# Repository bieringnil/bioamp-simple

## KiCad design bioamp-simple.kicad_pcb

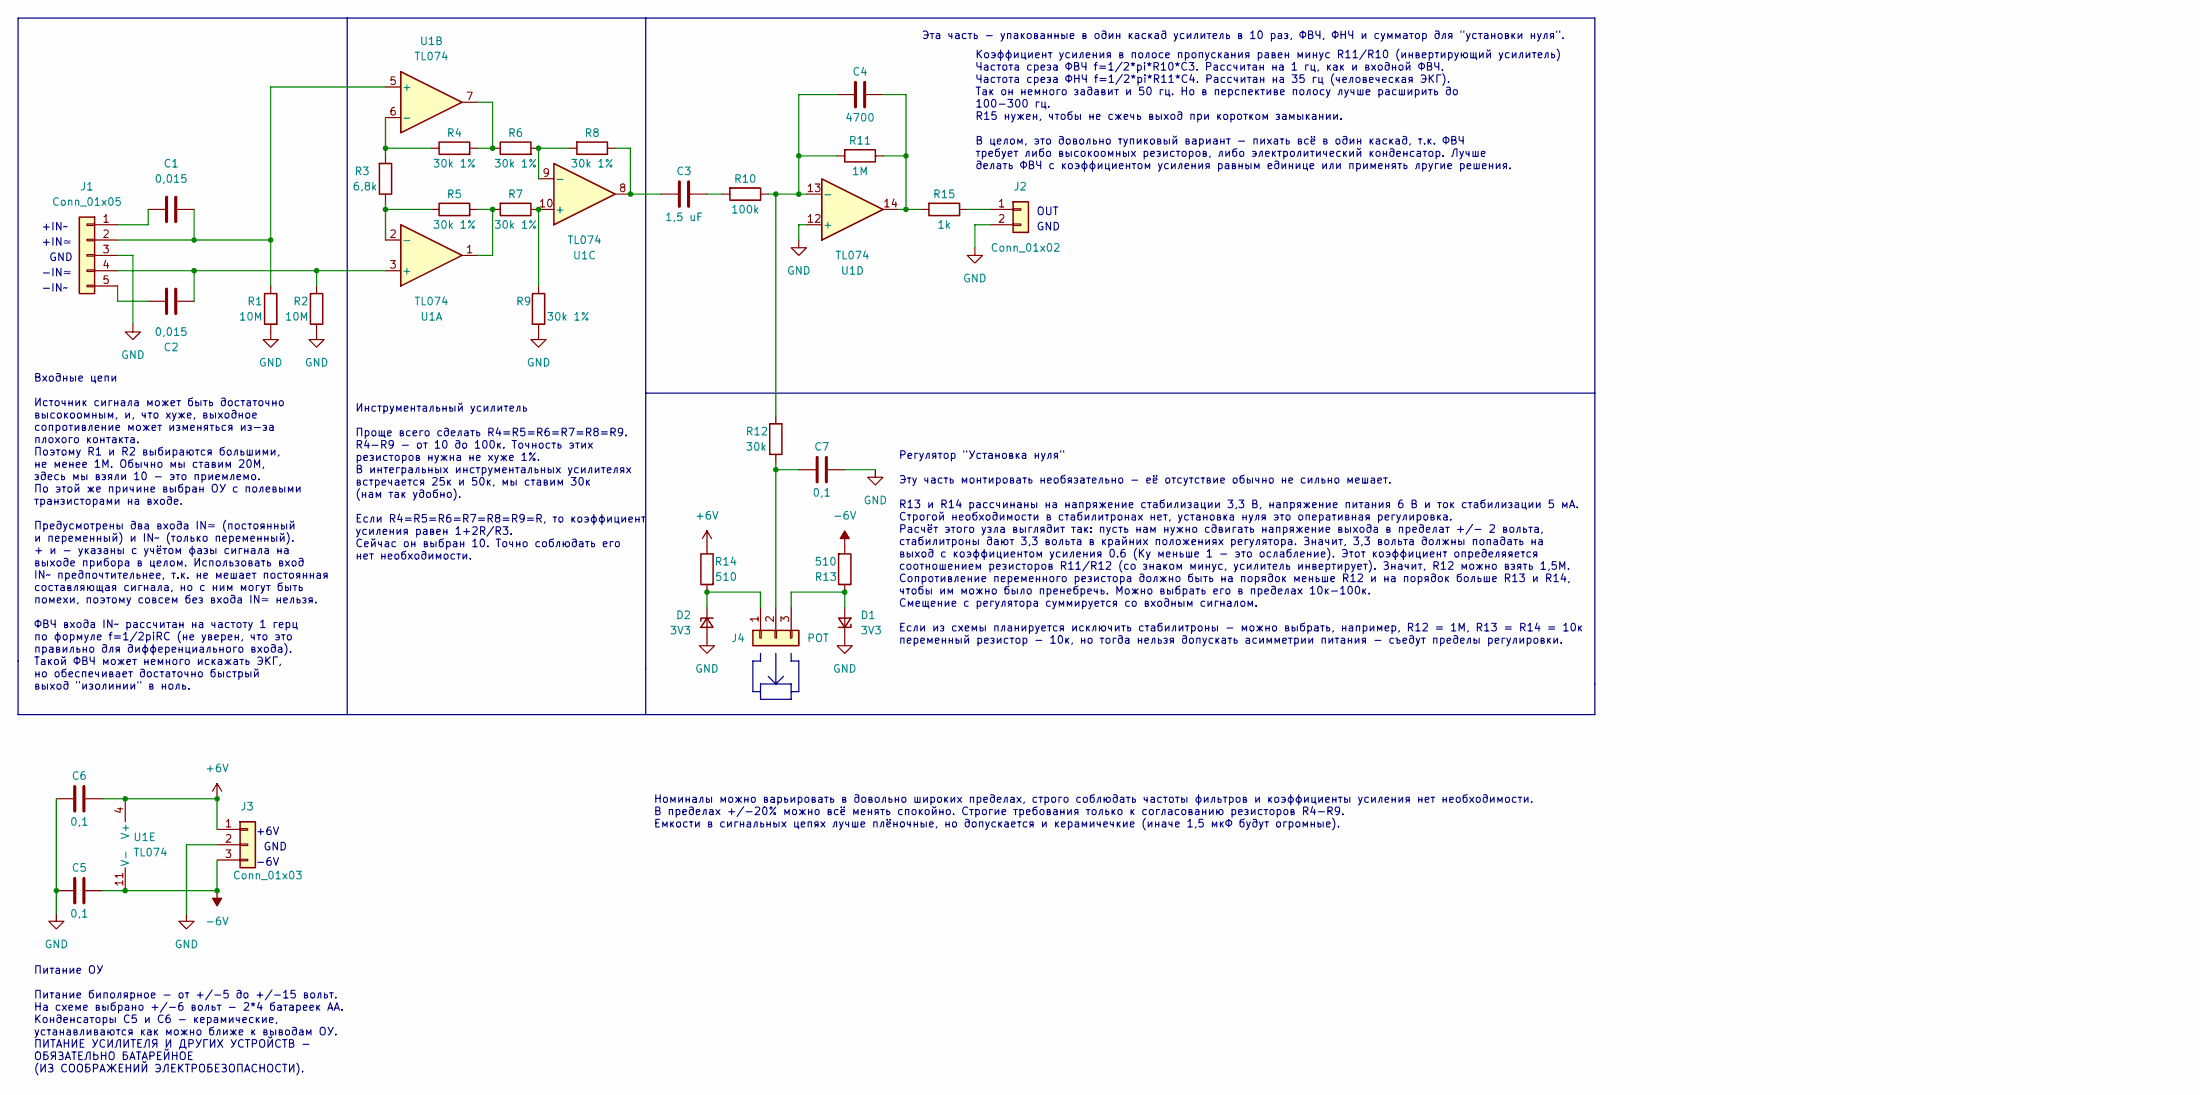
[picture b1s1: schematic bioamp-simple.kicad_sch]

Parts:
C1, C2: 0,015; C_Rect_L7.0mm_W4.5mm_P5.00mm
C3: 1,5 uF; C_Rect_L16.5mm_W5.0mm_P15.00mm_MKT
C4: 4700; C_Rect_L7.0mm_W4.5mm_P5.00mm
C5, C6, C7: 0,1; C_Rect_L7.0mm_W4.5mm_P5.00mm
D1, D2: 3V3; D_A-405_P10.16mm_Horizontal
J1: Conn_01x05; SolderWire-0.5sqmm_1x05_P4.6mm_D0.9mm_OD2.1mm
J2: Conn_01x02; SolderWire-0.5sqmm_1x02_P4.6mm_D0.9mm_OD2.1mm
J3: Conn_01x03; SolderWire-0.5sqmm_1x03_P4.6mm_D0.9mm_OD2.1mm
J4: POT; SolderWire-0.5sqmm_1x03_P4.6mm_D0.9mm_OD2.1mm
R1, R2: 10M; R_Axial_DIN0207_L6.3mm_D2.5mm_P15.24mm_Horizontal
R3: 6,8k; R_Axial_DIN0207_L6.3mm_D2.5mm_P10.16mm_Horizontal
R4, R5, R8: 30k 1%; R_Axial_DIN0207_L6.3mm_D2.5mm_P2.54mm_Vertical
R6, R7, R9: 30k 1%; R_Axial_DIN0207_L6.3mm_D2.5mm_P10.16mm_Horizontal
R10: 100k; R_Axial_DIN0207_L6.3mm_D2.5mm_P10.16mm_Horizontal
R11: 1M; R_Axial_DIN0207_L6.3mm_D2.5mm_P2.54mm_Vertical
R12: 30k; R_Axial_DIN0207_L6.3mm_D2.5mm_P10.16mm_Horizontal
R13, R14: 510; R_Axial_DIN0207_L6.3mm_D2.5mm_P10.16mm_Horizontal
R15: 1k; R_Axial_DIN0207_L6.3mm_D2.5mm_P10.16mm_Horizontal
U1: TL074; DIP-14_W7.62mm_LongPads

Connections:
+6V: C6.2, J3.1, R14.1, U1.4 (V+)
-6V: C5.2, J3.3, R13.2, U1.11 (V-)
GND: C5.1, C6.1, C7.2, D1.1 (K), D2.2 (A), J1.3, J2.2, J3.2, R1.2, R2.1, R9.2, U1.12 (+)
unnamed: C3.1, R8.1, U1.8
unnamed: C3.2, R10.2
unnamed: C4.2, R11.1, R15.2, U1.14
unnamed: D1.2 (A), J4.3, R13.1
unnamed: D2.1 (K), J4.1, R14.2
unnamed: C1.1, J1.1
unnamed: C1.2, J1.2, R1.1, U1.5 (+)
unnamed: C2.2, J1.4, R2.2, U1.3 (+)
unnamed: C2.1, J1.5
unnamed: J2.1, R15.1
unnamed: C7.1, J4.2, R12.2
unnamed: R4.2, R6.1, U1.7
unnamed: R5.2, R7.2, U1.1
unnamed: R3.1, R5.1, U1.2 (-)
unnamed: R3.2, R4.1, U1.6 (-)
unnamed: R7.1, R9.1, U1.10 (+)
unnamed: R6.2, R8.2, U1.9 (-)
unnamed: C4.1, R10.1, R11.2, R12.1, U1.13 (-)

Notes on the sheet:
+IN~
Входные цепи Источник сигнала может быть достаточно высокоомным, и, что хуже, выходное сопротивление может изменяться из-за плохого контакта. Поэтому R1 и R2 выбираются большими, не менее 1М. Обычно мы ставим 20М, здесь мы взяли 10 - это приемлемо. По этой же причине выбран ОУ с полевыми транзистор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
+6V
OUT
Питание ОУ Питание биполярное - от +/-5 до +/-15 вольт. На схеме выбрано +/-6 вольт - 2*4 батареек АА. Конденсаторы C5 и C6 - керамические, устанавливаются как можно ближе к выводам ОУ. ПИТАНИЕ УСИЛИТЕЛЯ И ДРУГИХ УСТРОЙСТВ - ОБЯЗАТЕЛЬНО БАТАРЕЙНОЕ (ИЗ СООБРАЖЕНИЙ ЭЛЕКТРОБЕЗОПАСНОСТИ).
-IN≃
Инструментальный усилитель Проще всего сделать R4=R5=R6=R7=R8=R9. R4-R9 - от 10 до 100к. Точность этих резисторов нужна не хуже 1%. В интегральных инструментальных усилителях встречается 25к и 50к, мы ставим 30к (нам так удобно). Если R4=R5=R6=R7=R8=R9=R, то коэффициент усиления равен 1+2R/R3. Сейч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
Эта часть - упакованные в один каскад усилитель в 10 раз, ФВЧ, ФНЧ и сумматор для "установки нуля".
GND
Регулятор "Установка нуля" Эту часть монтировать необязательно - её отсутствие обычно не сильно мешает. R13 и R14 рассчинаны на напряжение стабилизации 3,3 В, напряжение питания 6 В и ток стабилизации 5 мА. Строгой необходимости в стабилитронах нет, установка нуля это оперативная регулировка. Расчё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
-6V
Коэффициент усиления в полосе пропускания равен минус R11/R10 (инвертирующий усилитель) Частота среза ФВЧ f=1/2*pi*R10*C3. Рассчитан на 1 гц, как и входной ФВЧ. Частота среза ФНЧ f=1/2*pi*R11*C4. Рассчитан на 35 гц (человеческая ЭКГ). Так он немного задавит и 50 гц. Но в перспективе полосу лучше ра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
Номиналы можно варьировать в довольно широких пределах, строго соблюдать частоты фильтров и коэффициенты усиления нет необходимости. В пределах +/-20% можно всё менять спокойно. Строгие требования только к согласованию резисторов R4-R9. Емкости в сигнальных цепях лучше плёночные, но допускается и к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
+IN≃
-IN~

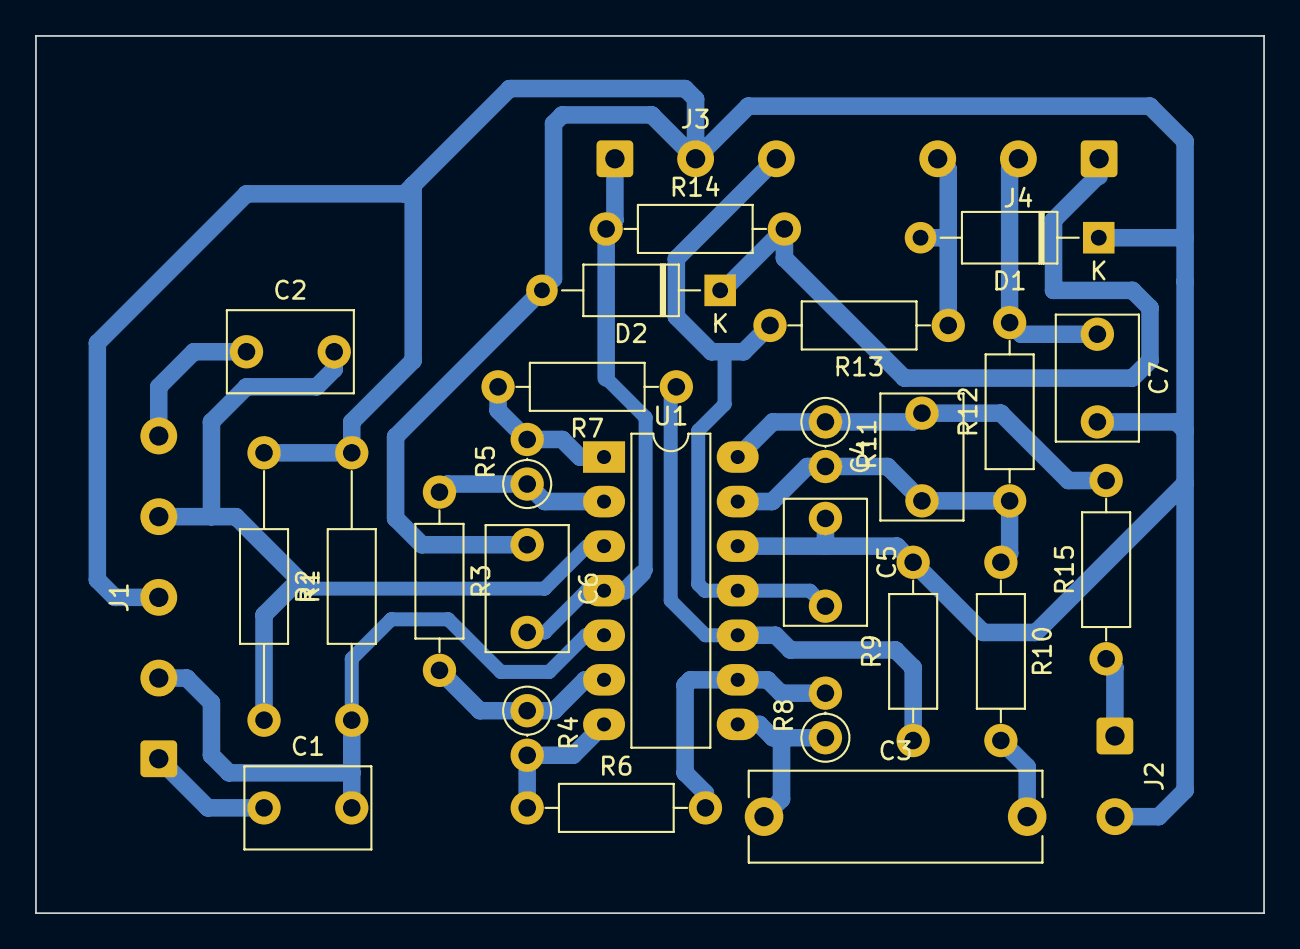
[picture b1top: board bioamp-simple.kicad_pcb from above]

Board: 2 copper layers, 70.0 x 50.0 mm, 29 parts (0 on the bottom side), 21 nets.

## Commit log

2024-01-02 earth zone added
